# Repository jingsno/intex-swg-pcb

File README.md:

# Intex SWG automaton

This is a PCB for Intex SWG Automation at
https://github.com/tonyflores1006/intex-swg-iot

Discussion here
https://www.troublefreepool.com/threads/automation-of-intex-swg.228606/

This PCB is suitable for both the TM1650 and the PIC16F88 version of the display board.

Software for the "non TM1650" (18 pin) version of the display board is under development.
(Current status of non released development version of the software, allows for fullt control of the Intex SWG from a web interface.)

Known models without the TM1650 chip:
* Intex Krystal Clear salt water system® ECO 6220 / CG-26670 (7-led/5 buttons), Max 56800 Liters

*PCB for Intex SWG automation*

## Schematic

Link to [PDF Schematic](docs/intex-swg-pcb.pdf)

## Parts list

| Part            |             |
|-----------------|-------------|
| ESP32-DevkitC ext antenna |  https://www.digikey.com/en/products/detail/espressif-systems/ESP32-DEVKITC-32U/9357002 | 
| IRM-03-5 | https://www.digikey.com/en/products/detail/mean-well-usa-inc/IRM-03-5/7704640 |
| Level shifter to/from 5V/3.3V | https://www.aliexpress.com/item/1005001621978054.html | 
| 3.3V Relay module | https://www.aliexpress.com/item/32884967707.html | 
| 2x Female and 1x Male XH2.54 4pin connectors | https://www.aliexpress.com/item/4000126563819.html | 
| Stepper Motor cables/wire XH2.54 4pin | https://www.aliexpress.com/item/1005001361294507.html |
| Fuse 3A / 250V | https://www.aliexpress.com/item/32702176964.html | 
| 2-pin screw terminal | https://www.aliexpress.com/item/1005002971443405.html  | 
| 3-pin screw terminal | https://www.aliexpress.com/item/1005002971443405.html  | 
| 2x 3-pin header with jumper (or wire) | https://www.aliexpress.com/item/32873263301.html  |

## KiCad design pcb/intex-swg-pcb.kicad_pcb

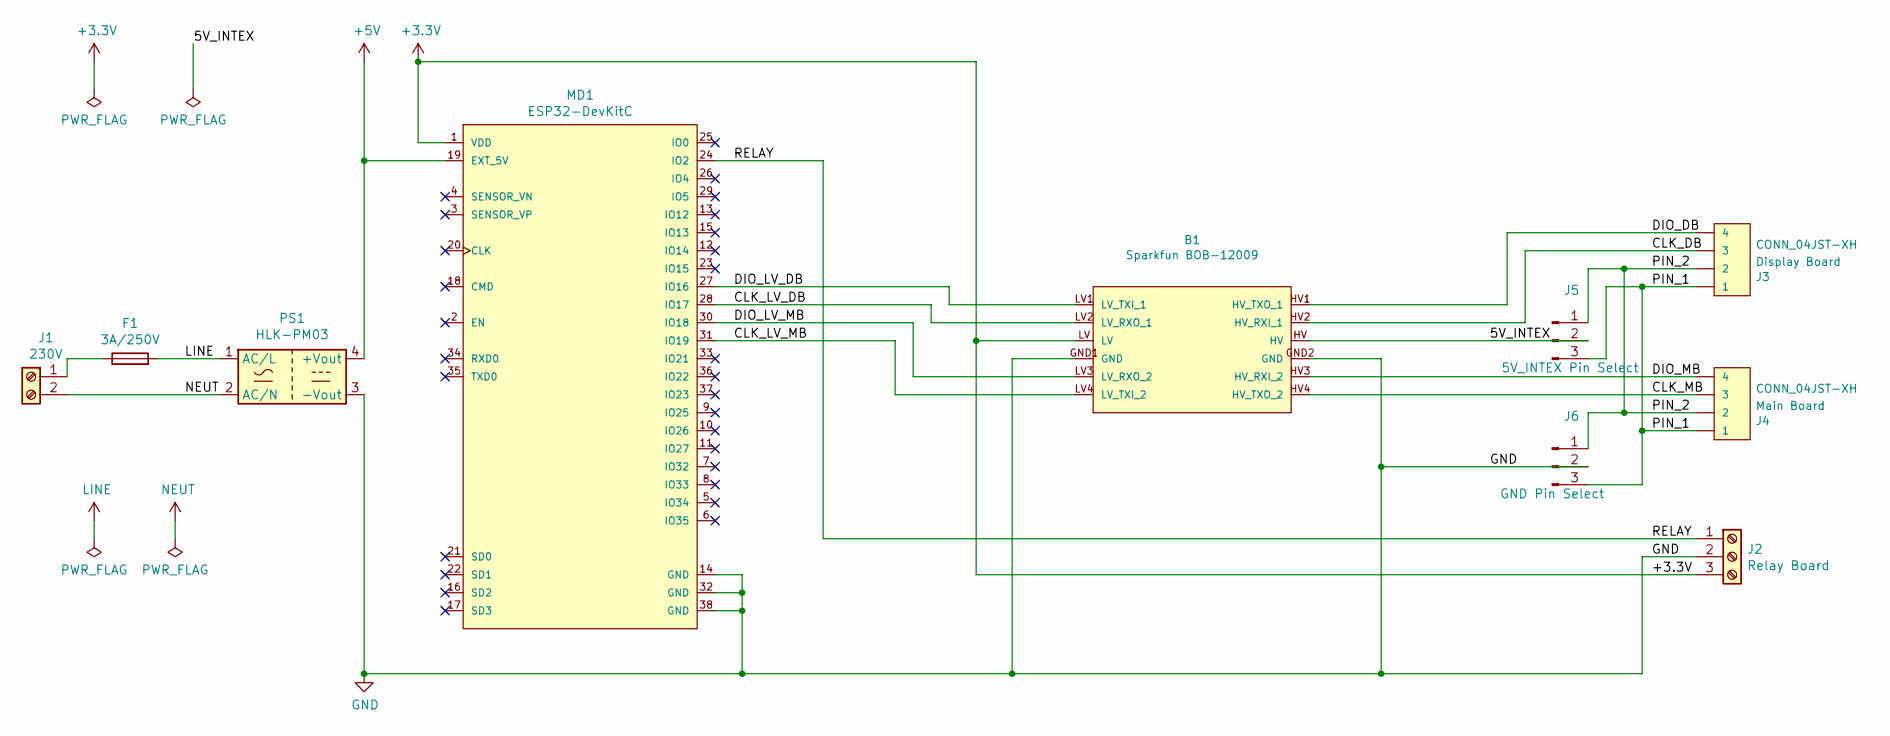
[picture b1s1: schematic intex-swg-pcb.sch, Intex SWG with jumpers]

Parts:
B1: Sparkfun BOB-12009; SPARKFUN_LOGIC_LEVEL_CONVERTER; digi-key part number 1568-1209-ND
F1: 3A/250V; Fuse_Littelfuse-LVR100
J1: 230V; TerminalBlock_Phoenix_MKDS-1,5-2_1x02_P5.00mm_Horizontal
J2: Relay Board; TerminalBlock_Phoenix_MKDS-1,5-3_1x03_P5.00mm_Horizontal
J3: Display Board; JST_XH_B4B-XH-A_1x04_P2.50mm_Vertical; digi-key part number 455-2249-ND
J4: Main Board; JST_XH_B4B-XH-A_1x04_P2.50mm_Vertical; digi-key part number 455-2249-ND
J5: 5V_INTEX Pin Select; PinHeader_1x03_P2.54mm_Vertical
J6: GND Pin Select; PinHeader_1x03_P2.54mm_Vertical
MD1: ESP32-DevKitC; Espressif-ESP32-DevKitC_V4-0-0-MFG; mouser part number 356-ESP32-DEVKITC
PS1: HLK-PM03; Converter_ACDC_HiLink_HLK-PMxx

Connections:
+3V3: B1.LV, J2.3, MD1.1 (VDD)
+5V: MD1.19 (EXT_5V), PS1.4 (+Vout)
/5V_INTEX: B1.HV, J5.2
/CLK_DB: B1.HV2 (HV_RXI_1), J3.3
/CLK_LV_DB: B1.LV2 (LV_RXO_1), MD1.28 (IO17)
/CLK_LV_MB: B1.LV4 (LV_TXI_2), MD1.31 (IO19)
/CLK_MB: B1.HV4 (HV_TXO_2), J4.3
/DIO_DB: B1.HV1 (HV_TXO_1), J3.4
/DIO_LV_DB: B1.LV1 (LV_TXI_1), MD1.27 (IO16)
/DIO_LV_MB: B1.LV3 (LV_RXO_2), MD1.30 (IO18)
/DIO_MB: B1.HV3 (HV_RXI_2), J4.4
/PIN_1: J3.1, J4.1, J5.3, J6.3
/PIN_2: J3.2, J4.2, J5.1, J6.1
/RELAY: J2.1, MD1.24 (IO2)
GND: B1.GND1 (GND), B1.GND2 (GND), J2.2, J6.2, MD1.14 (GND), MD1.32 (GND), MD1.38 (GND), PS1.3 (-Vout)
LINE: F1.2, PS1.1 (AC/L)
NEUT: J1.2, PS1.2 (AC/N)
unnamed: F1.1, J1.1

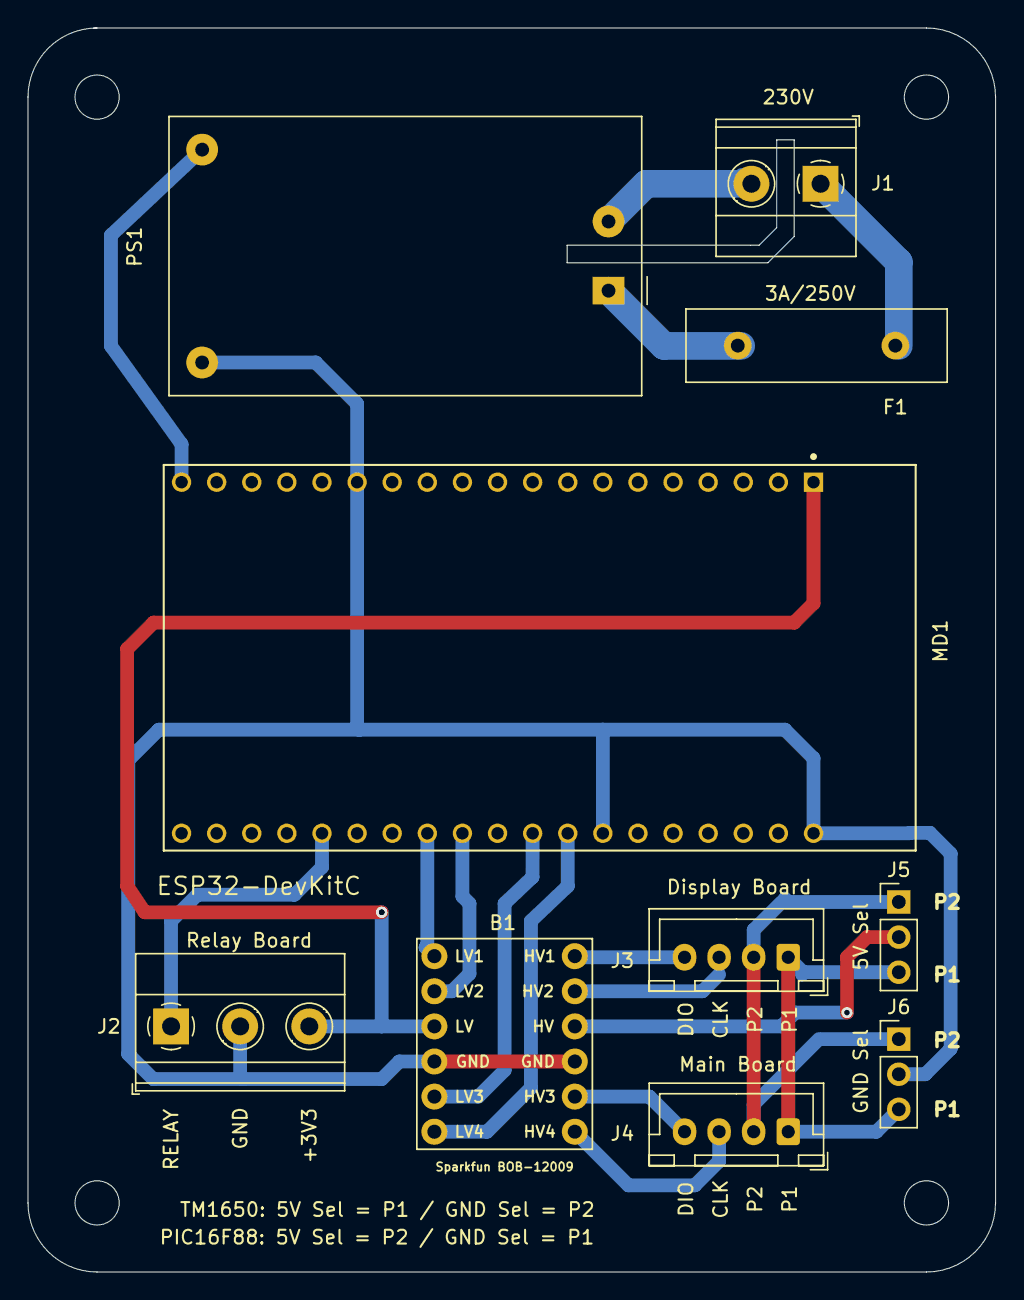
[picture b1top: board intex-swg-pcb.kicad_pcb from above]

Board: 2 copper layers, 70.0 x 90.0 mm, 10 parts (0 on the bottom side), 18 nets.

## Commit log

2022-05-22 Removed non updated BOM files
2022-05-22 Updated .gitignore
2022-06-06 Swapped relay to GPIO2
2022-06-06 Uploaded protocol documentation/code samples
2022-06-06 Corrected typo
2022-06-06 Set datalines high on ESP32 boot
2022-06-06 Added parts list
2022-06-07 Clean, fixed, and expanded Demo_ESP32 code
2022-06-09 Cleanup
2022-06-11 Corrected top left mounting hole, that was 0.24mm offset
